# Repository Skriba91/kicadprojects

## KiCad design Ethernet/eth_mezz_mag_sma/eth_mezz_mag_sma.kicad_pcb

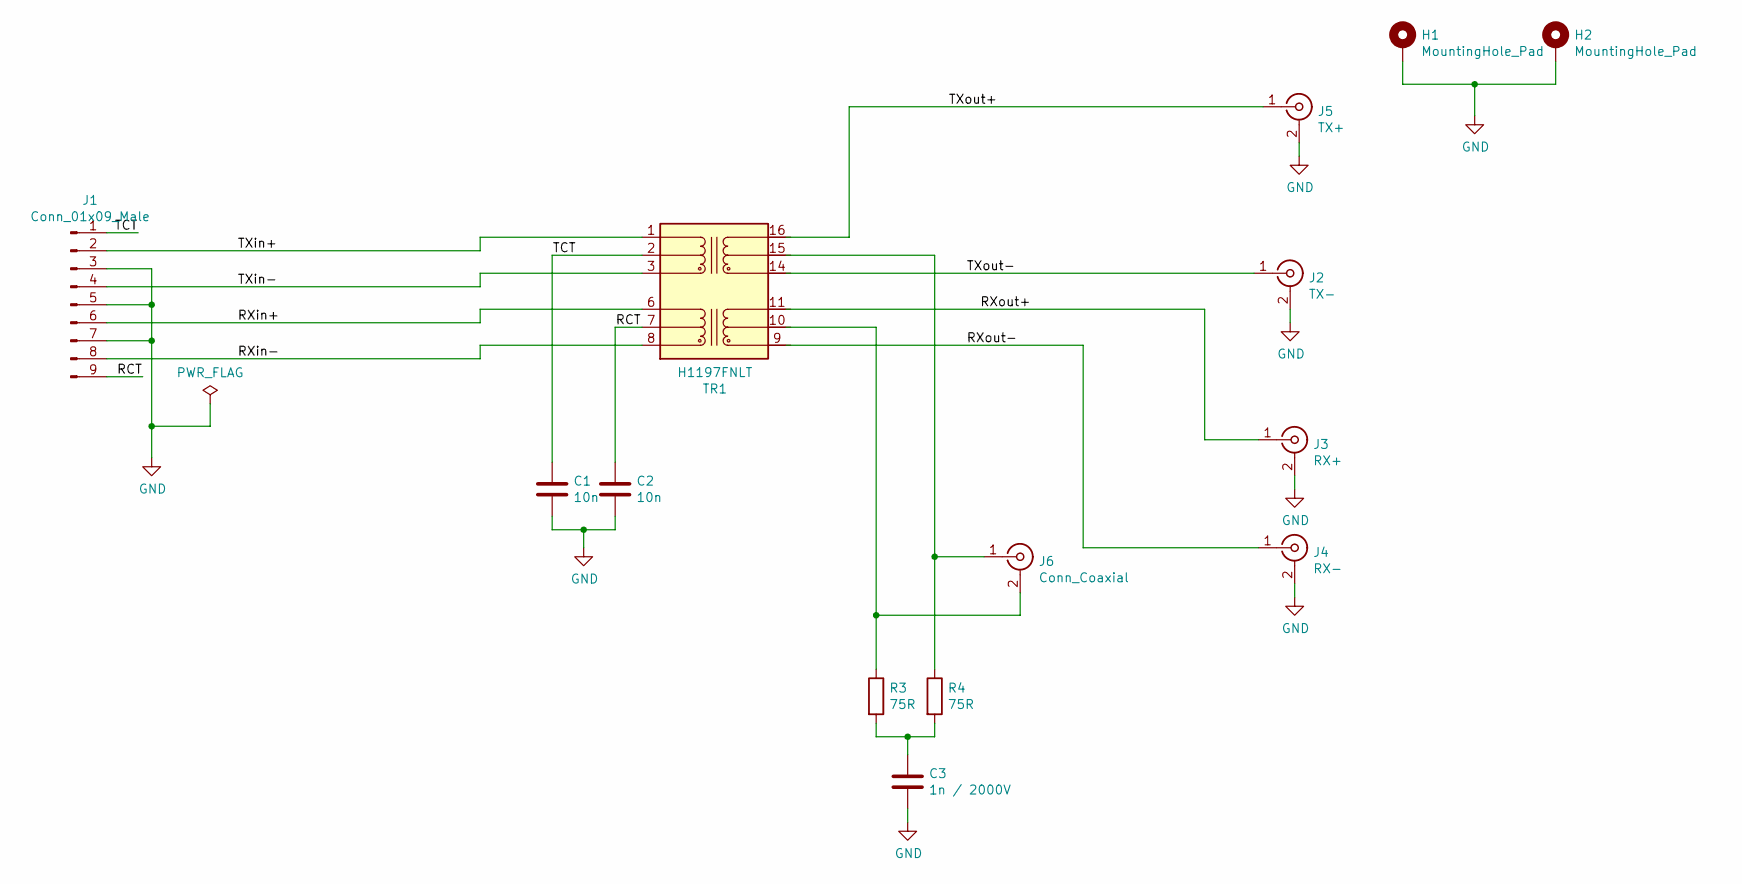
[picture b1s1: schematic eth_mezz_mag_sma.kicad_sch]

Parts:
C1, C2: 10n; C_0805_2012Metric_Pad1.18x1.45mm_HandSolder
C3: 1n / 2000V; R_1206_3216Metric_Pad1.42x1.75mm_HandSolder
H1, H2: MountingHole_Pad; MountingHole_3.2mm_M3_Pad_Via
J1: Conn_01x09_Male; mezzanine_9p_10162582-1134109LF_Conan_1mm
J2: TX-; SMA_Amphenol_132134_Vertical
J3: RX+; SMA_Amphenol_132134_Vertical
J4: RX-; SMA_Amphenol_132134_Vertical
J5: TX+; SMA_Amphenol_132134_Vertical
J6: Conn_Coaxial; BNC_TEConnectivity_1478204_Vertical
R3, R4: 75R; R_0805_2012Metric_Pad1.20x1.40mm_HandSolder
TR1: H1197FNLT; Transformer_Ethernet_Bourns_PT61017PEL

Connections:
/RCT: C2.1, J1.9, TR1.7 (C_RD)
/RXin+: J1.6, TR1.6 (RD+)
/RXin-: J1.8, TR1.8 (RD-)
/RXout+: J3.1 (In), TR1.11 (RX+)
/RXout-: J4.1 (In), TR1.9 (RX-)
/TCT: C1.1, J1.1, TR1.2 (C_TD)
/TXin+: J1.2, TR1.1 (TD+)
/TXin-: J1.4, TR1.3 (TD-)
/TXout+: J5.1 (In), TR1.16 (TX+)
/TXout-: J2.1 (In), TR1.14 (TX-)
GND: C1.2, C2.2, C3.2, H1.1, H2.1, J1.3, J1.5, J1.7, J2.2 (Ext), J3.2 (Ext), J4.2 (Ext), J5.2 (Ext)
unnamed: C3.1, R3.2, R4.2
unnamed: J6.1 (In), R4.1, TR1.15 (C_TX)
unnamed: J6.2 (Ext), R3.1, TR1.10 (C_RX)

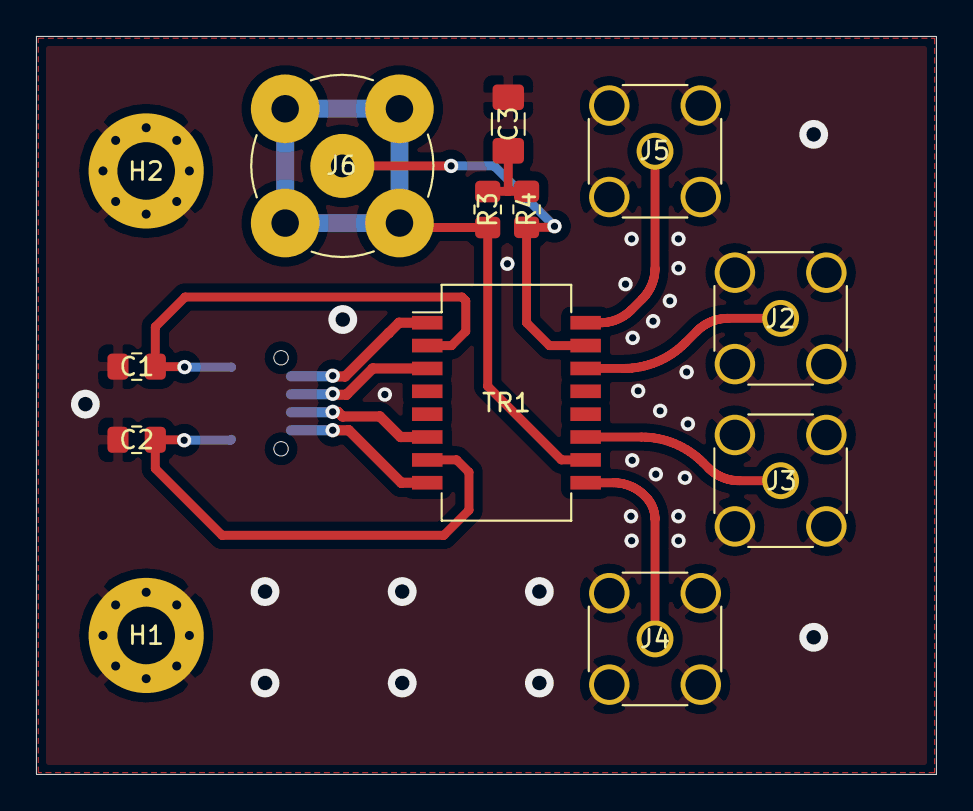
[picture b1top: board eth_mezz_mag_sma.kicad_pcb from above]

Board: 2 copper layers, 50.0 x 41.0 mm, 14 parts (1 on the bottom side), 14 nets.

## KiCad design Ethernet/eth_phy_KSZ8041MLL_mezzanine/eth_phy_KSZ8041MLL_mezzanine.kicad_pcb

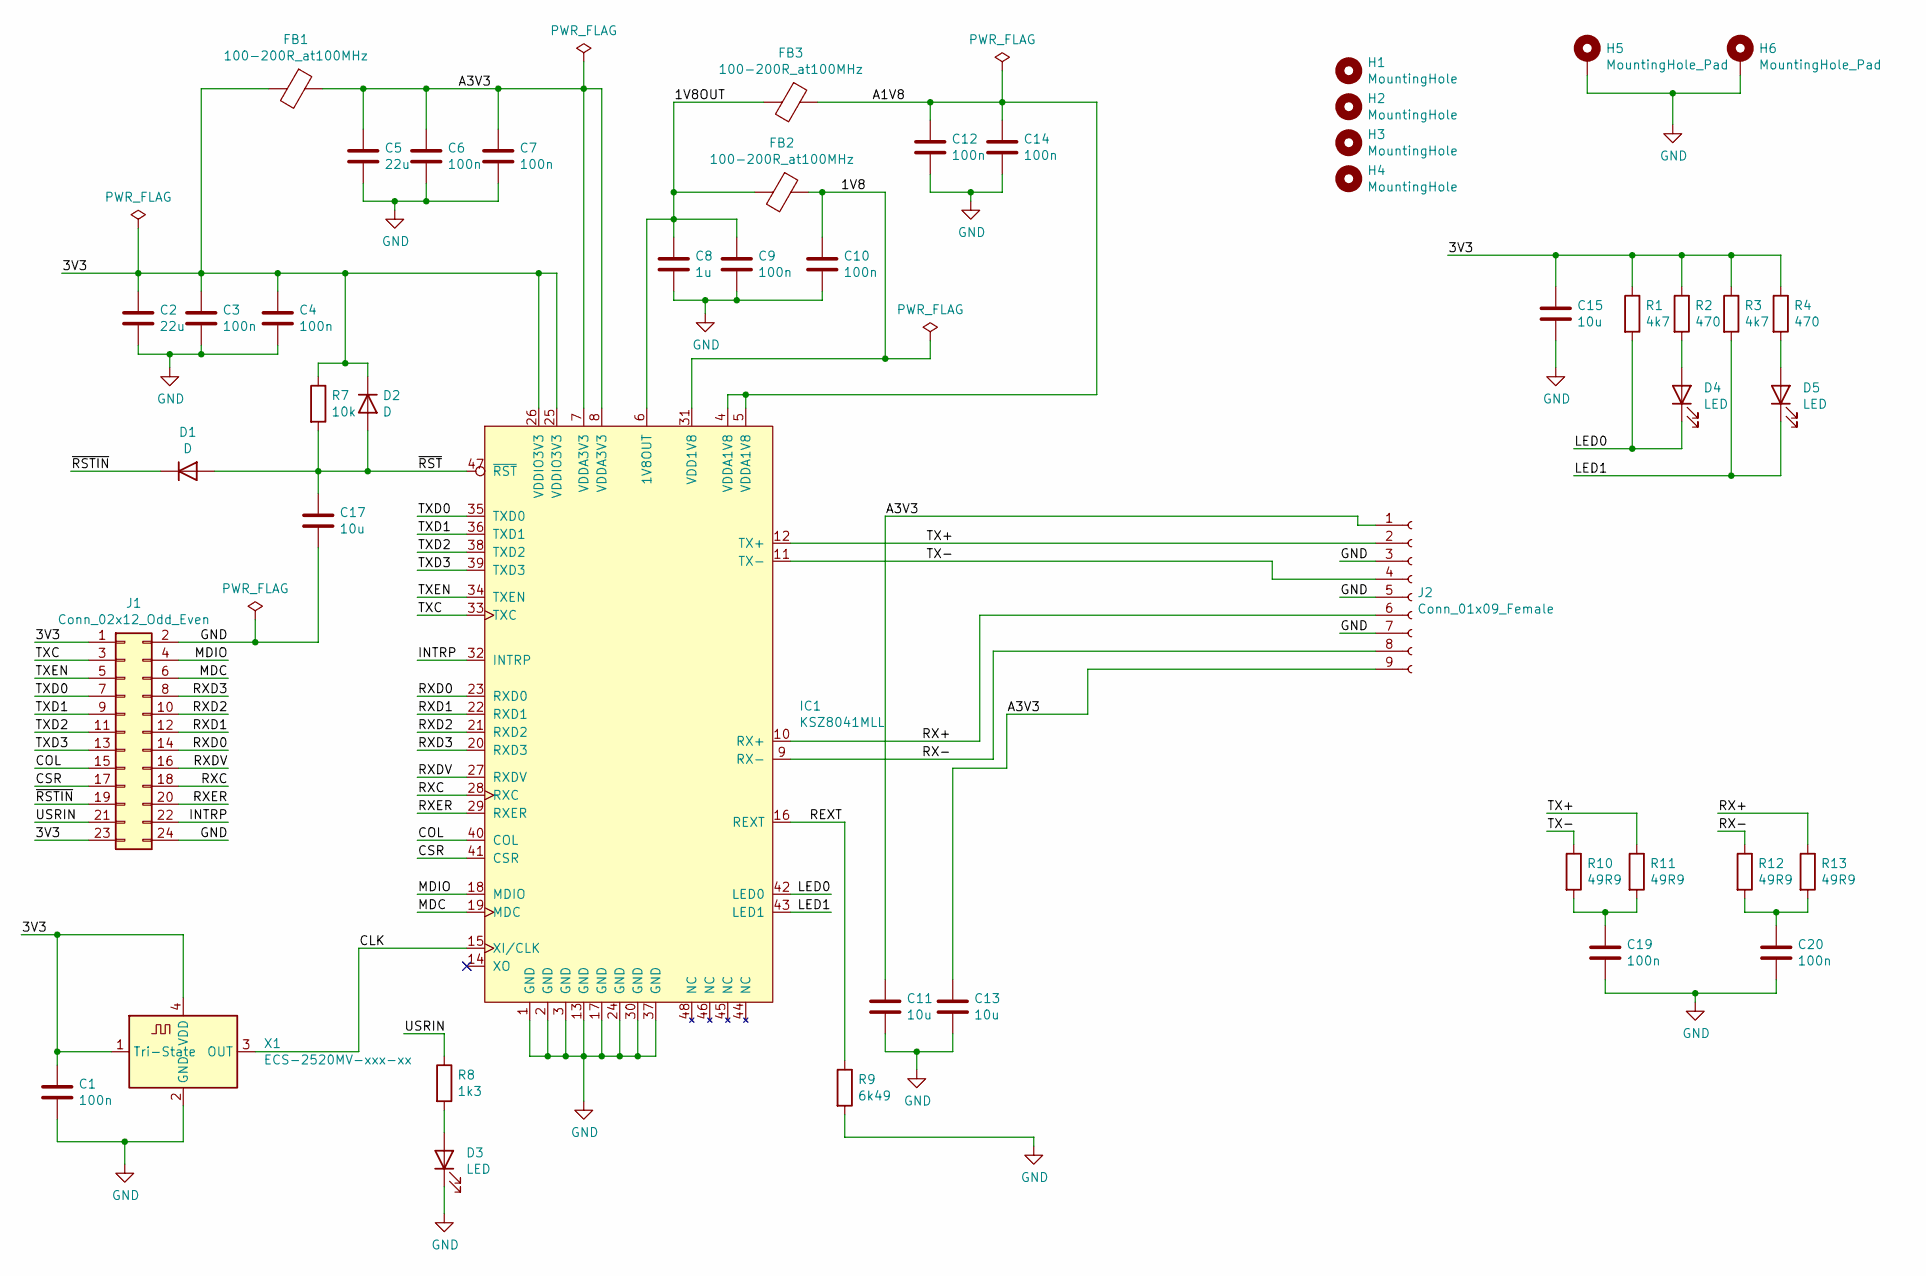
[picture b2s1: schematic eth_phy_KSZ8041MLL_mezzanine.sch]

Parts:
C1, C3, C4, C6, C7, C9, C10, C12, C14, C19, C20: 100n; C_0603_1608Metric_Pad1.08x0.95mm_HandSolder
C2: 22u; C_1206_3216Metric_Pad1.33x1.80mm_HandSolder
C5: 22u; C_1206_3216Metric_Pad1.42x1.75mm_HandSolder
C8: 1u; C_0603_1608Metric_Pad1.08x0.95mm_HandSolder
C11, C13: 10u; C_0603_1608Metric_Pad1.08x0.95mm_HandSolder
C15: 10u; C_0805_2012Metric_Pad1.18x1.45mm_HandSolder
C17: 10u; C_1206_3216Metric_Pad1.42x1.75mm_HandSolder
D1, D2: D; D_MiniMELF_Handsoldering
D3, D4, D5: LED; LED_0805_2012Metric_Pad1.15x1.40mm_HandSolder
FB1, FB2, FB3: 100-200R_at100MHz; L_0805_2012Metric_Pad1.15x1.40mm_HandSolder
H1, H2, H3, H4: MountingHole; MountingHole_3.2mm_M3_Pad_Via
H5, H6: MountingHole_Pad; MountingHole_3.2mm_M3_Pad_Via
IC1: KSZ8041MLL; LQFP-48_7x7mm_P0.5mm
J1: Conn_02x12_Odd_Even; PinHeader_2x12_P2.54mm_Horizontal
J2: Conn_01x09_Female; mezzanine_9p_10162582-1134109LF_Conan_1mm
R1, R3: 4k7; R_0805_2012Metric_Pad1.20x1.40mm_HandSolder
R2, R4: 470; R_0805_2012Metric_Pad1.20x1.40mm_HandSolder
R7: 10k; R_0603_1608Metric_Pad1.05x0.95mm_HandSolder
R8: 1k3; R_0603_1608Metric_Pad1.05x0.95mm_HandSolder
R9: 6k49; R_0603_1608Metric_Pad1.05x0.95mm_HandSolder
R10, R11, R12, R13: 49R9; R_0603_1608Metric_Pad1.05x0.95mm_HandSolder
X1: ECS-2520MV-xxx-xx; Oscillator_SMD_ECS_2520MV-xxx-xx-4Pin_2.5x2.0mm_HANDSOLD

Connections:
/1V8: C10.1, FB2.1, IC1.31 (VDD1V8)
/1V8OUT: C8.1, C9.1, FB2.2, FB3.2, IC1.6 (1V8OUT)
/3V3: C1.1, C2.1, C3.1, C4.1, C15.1, D2.1 (K), FB1.2, IC1.25 (VDDIO3V3), IC1.26 (VDDIO3V3), J1.1, J1.23, R1.1, R2.1, R3.1, R4.1, R7.1, X1.1 (Tri-State), X1.4 (VDD)
/A1V8: C12.1, C14.1, FB3.1, IC1.4 (VDDA1V8), IC1.5 (VDDA1V8)
/A3V3: C5.1, C6.1, C7.1, C11.1, C13.1, FB1.1, IC1.7 (VDDA3V3), IC1.8 (VDDA3V3), J2.1, J2.9
/CLK: IC1.15 (XI/CLK), X1.3 (OUT)
/COL: IC1.40 (COL), J1.15
/CSR: IC1.41 (CSR), J1.17
/INTRP: IC1.32 (INTRP), J1.22
/LED0: D4.1 (K), IC1.42 (LED0), R1.2
/LED1: D5.1 (K), IC1.43 (LED1), R3.2
/MDC: IC1.19 (MDC), J1.6
/MDIO: IC1.18 (MDIO), J1.4
/REXT: IC1.16 (REXT), R9.1
/RX+: IC1.10 (RX+), J2.6, R13.1
/RX-: IC1.9 (RX-), J2.8, R12.1
/RXC: IC1.28 (RXC), J1.18
/RXD0: IC1.23 (RXD0), J1.14
/RXD1: IC1.22 (RXD1), J1.12
/RXD2: IC1.21 (RXD2), J1.10
/RXD3: IC1.20 (RXD3), J1.8
/RXDV: IC1.27 (RXDV), J1.16
/RXER: IC1.29 (RXER), J1.20
/TX+: IC1.12 (TX+), J2.2, R11.1
/TX-: IC1.11 (TX-), J2.4, R10.1
/TXC: IC1.33 (TXC), J1.3
/TXD0: IC1.35 (TXD0), J1.7
/TXD1: IC1.36 (TXD1), J1.9
/TXD2: IC1.38 (TXD2), J1.11
/TXD3: IC1.39 (TXD3), J1.13
/TXEN: IC1.34 (TXEN), J1.5
/USRIN: J1.21, R8.1
/~RST: C17.1, D1.2 (A), D2.2 (A), IC1.47 (~RST), R7.2
/~RSTIN: D1.1 (K), J1.19
GND: C1.2, C2.2, C3.2, C4.2, C5.2, C6.2, C7.2, C8.2, C9.2, C10.2, C11.2, C12.2, C13.2, C14.2, C15.2, C17.2, C19.2, C20.2, D3.1 (K), H5.1, H6.1, IC1.1 (GND), IC1.2 (GND), IC1.3 (GND), IC1.13 (GND), IC1.17 (GND), IC1.24 (GND), IC1.30 (GND), IC1.37 (GND), J1.2, J1.24, J2.3, J2.5, J2.7, R9.2, X1.2 (GND)
unnamed: C19.1, R10.2, R11.2
unnamed: C20.1, R12.2, R13.2
unnamed: D3.2 (A), R8.2
unnamed: D4.2 (A), R2.2
unnamed: D5.2 (A), R4.2

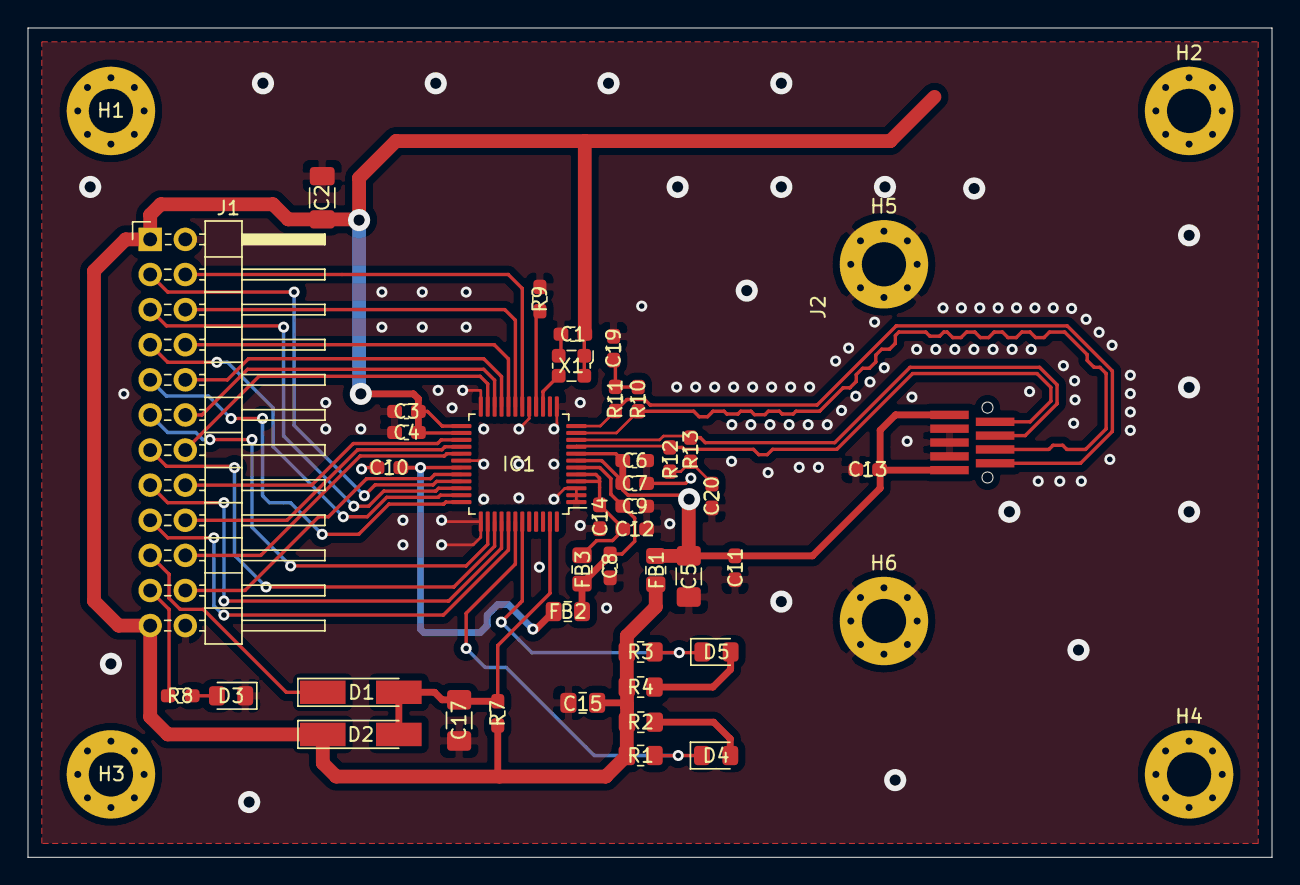
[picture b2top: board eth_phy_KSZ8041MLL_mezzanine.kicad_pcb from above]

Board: 2 copper layers, 90.0 x 60.0 mm, 47 parts (0 on the bottom side), 40 nets.

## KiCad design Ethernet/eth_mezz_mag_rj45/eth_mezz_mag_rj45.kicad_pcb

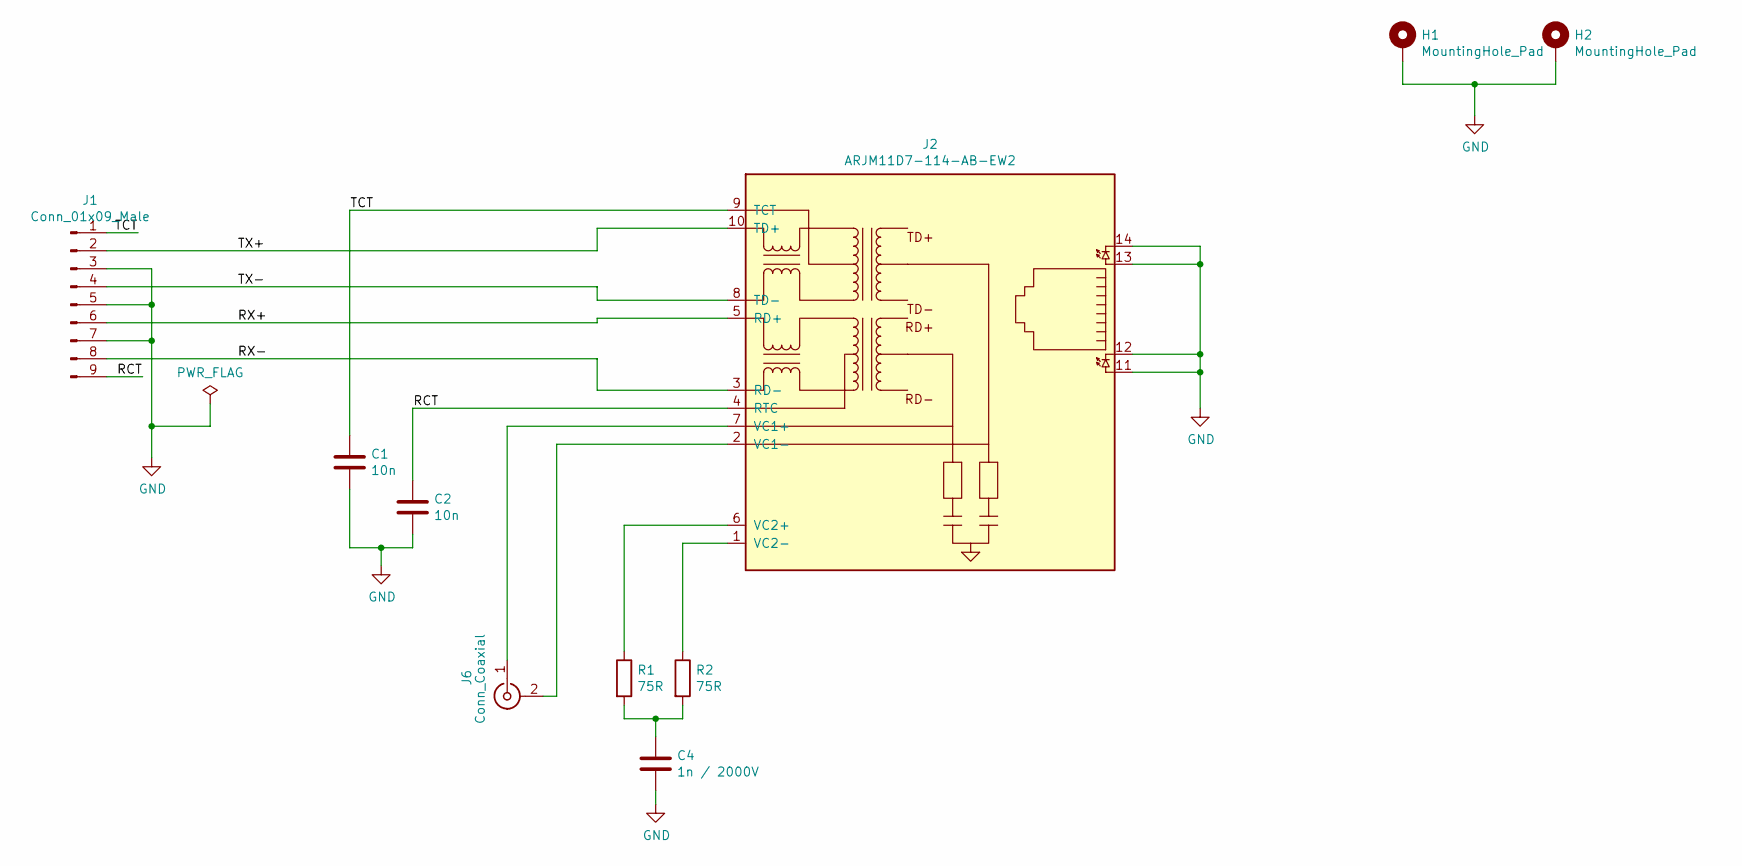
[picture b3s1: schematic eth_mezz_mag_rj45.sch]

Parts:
C1, C2: 10n; C_0805_2012Metric_Pad1.18x1.45mm_HandSolder
C4: 1n / 2000V; R_1206_3216Metric_Pad1.42x1.75mm_HandSolder
H1, H2: MountingHole_Pad; MountingHole_3.2mm_M3_Pad_Via
J1: Conn_01x09_Male; mezzanine_9p_10162582-1134109LF_Conan_1mm
J2: ARJM11D7-114-AB-EW2
J6: Conn_Coaxial; BNC_TEConnectivity_1478204_Vertical
R1, R2: 75R; R_0805_2012Metric_Pad1.20x1.40mm_HandSolder

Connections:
/RCT: C2.1, J1.9, J2.4 (RTC)
/RX+: J1.6, J2.5 (RD+)
/RX-: J1.8, J2.3 (RD-)
/TCT: C1.1, J1.1, J2.9 (TCT)
/TX+: J1.2, J2.10 (TD+)
/TX-: J1.4, J2.8 (TD-)
GND: C1.2, C2.2, C4.2, H1.1, H2.1, J1.3, J1.5, J1.7, J2.11, J2.12, J2.13, J2.14
unnamed: C4.1, R1.2, R2.2
unnamed: J2.1 (VC2-), R2.1
unnamed: J2.2 (VC1-), J6.2 (Ext)
unnamed: J2.6 (VC2+), R1.1
unnamed: J2.7 (VC1+), J6.1 (In)

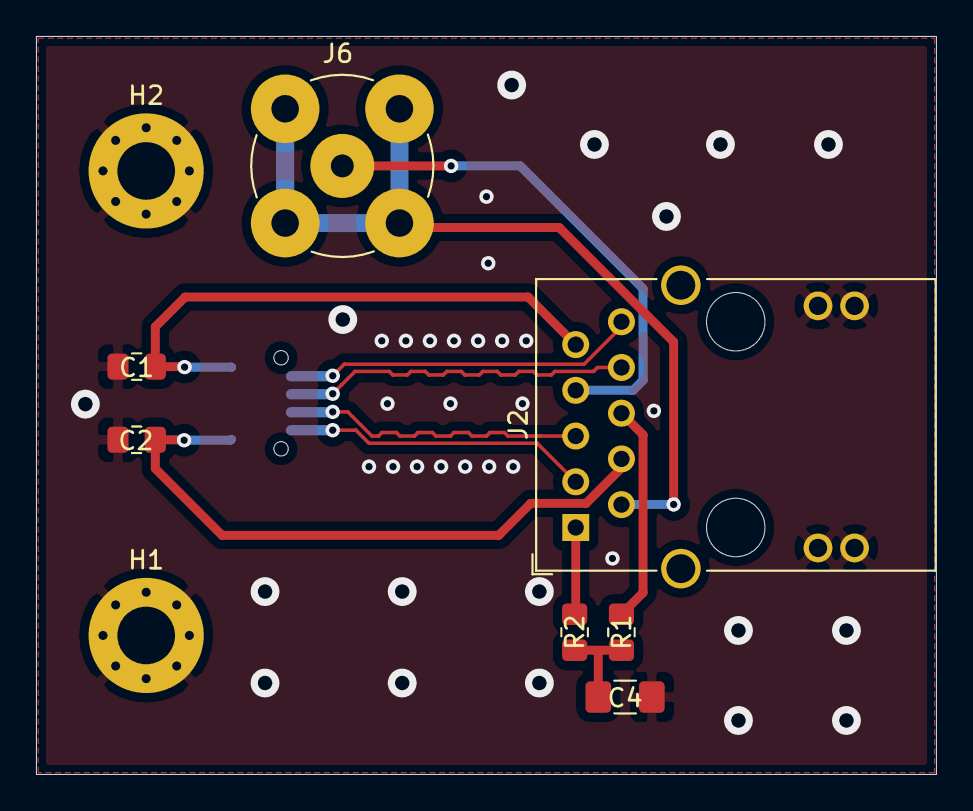
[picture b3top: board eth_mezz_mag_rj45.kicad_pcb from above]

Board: 2 copper layers, 50.0 x 41.0 mm, 10 parts (1 on the bottom side), 12 nets.

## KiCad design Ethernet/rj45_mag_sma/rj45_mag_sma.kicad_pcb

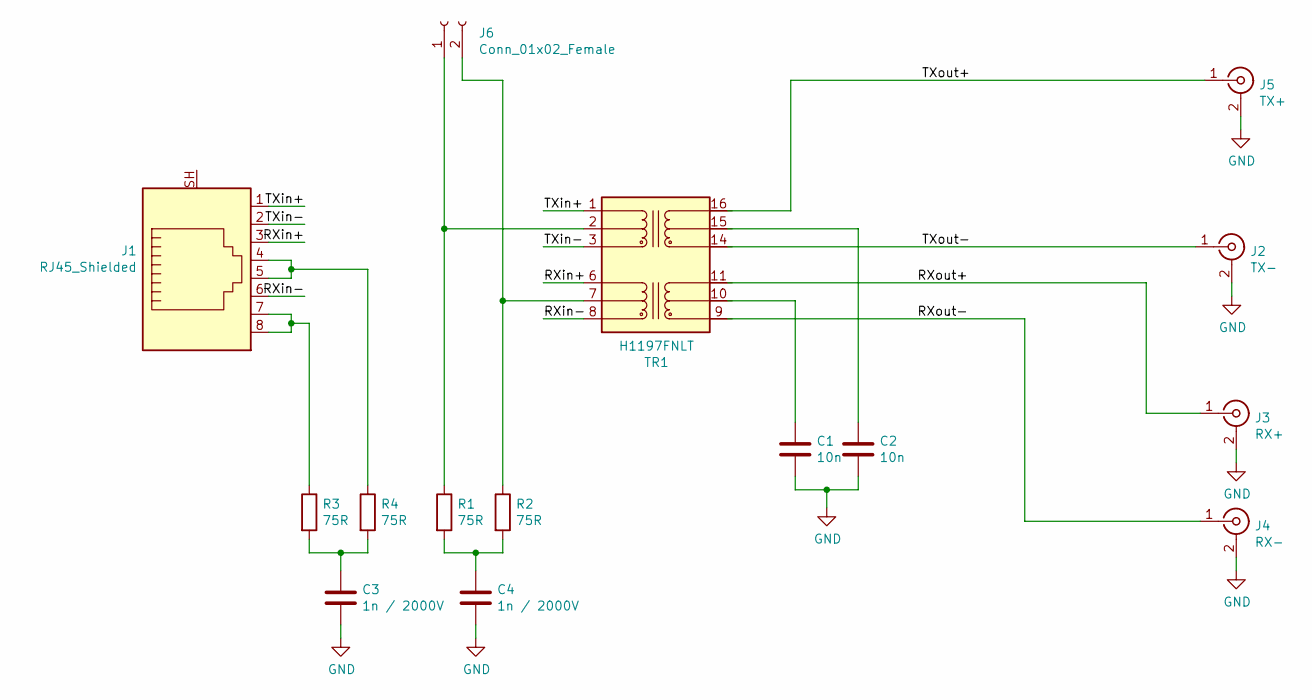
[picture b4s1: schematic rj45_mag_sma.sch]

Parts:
C1, C2: 10n; C_0805_2012Metric_Pad1.18x1.45mm_HandSolder
C3, C4: 1n / 2000V; R_1206_3216Metric_Pad1.42x1.75mm_HandSolder
J1: RJ45_Shielded; RJ45_Ninigi_GE
J2: TX-; SMA_Amphenol_132134_Vertical
J3: RX+; SMA_Amphenol_132134_Vertical
J4: RX-; SMA_Amphenol_132134_Vertical
J5: TX+; SMA_Amphenol_132134_Vertical
J6: Conn_01x02_Female; JWT_A3963_1x02_P3.96mm_Vertical
R1, R2, R3, R4: 75R; R_0805_2012Metric_Pad1.20x1.40mm_HandSolder
TR1: H1197FNLT; Transformer_Ethernet_Bourns_PT61017PEL

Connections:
/RXin+: J1.3, TR1.6 (RD+)
/RXin-: J1.6, TR1.8 (RD-)
/RXout+: J3.1 (In), TR1.11 (RX+)
/RXout-: J4.1 (In), TR1.9 (RX-)
/TXin+: J1.1, TR1.1 (TD+)
/TXin-: J1.2, TR1.3 (TD-)
/TXout+: J5.1 (In), TR1.16 (TX+)
/TXout-: J2.1 (In), TR1.14 (TX-)
GND: C1.2, C2.2, C3.2, C4.2, J1.SH, J2.2 (Ext), J3.2 (Ext), J4.2 (Ext), J5.2 (Ext)
unnamed: C1.1, TR1.10 (C_RX)
unnamed: C2.1, TR1.15 (C_TX)
unnamed: C3.1, R3.2, R4.2
unnamed: C4.1, R1.2, R2.2
unnamed: J1.4, J1.5, R4.1
unnamed: J1.7, J1.8, R3.1
unnamed: J6.1, R1.1, TR1.2 (C_TD)
unnamed: J6.2, R2.1, TR1.7 (C_RD)

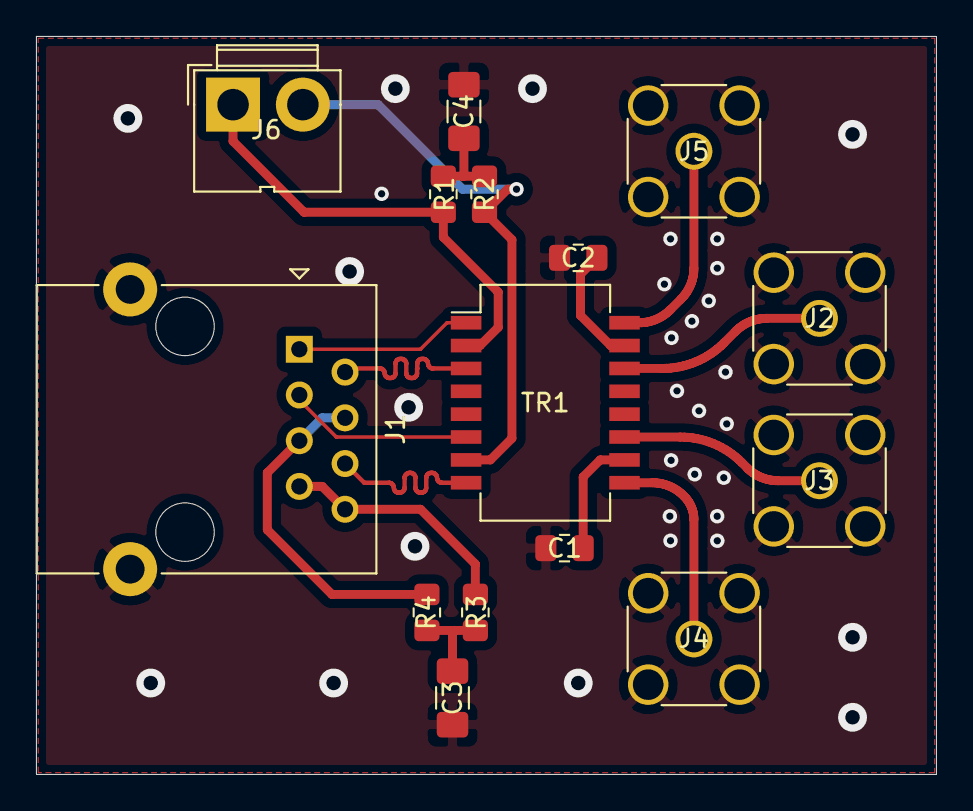
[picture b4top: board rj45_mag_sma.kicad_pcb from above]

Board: 2 copper layers, 50.0 x 41.0 mm, 15 parts (0 on the bottom side), 17 nets.

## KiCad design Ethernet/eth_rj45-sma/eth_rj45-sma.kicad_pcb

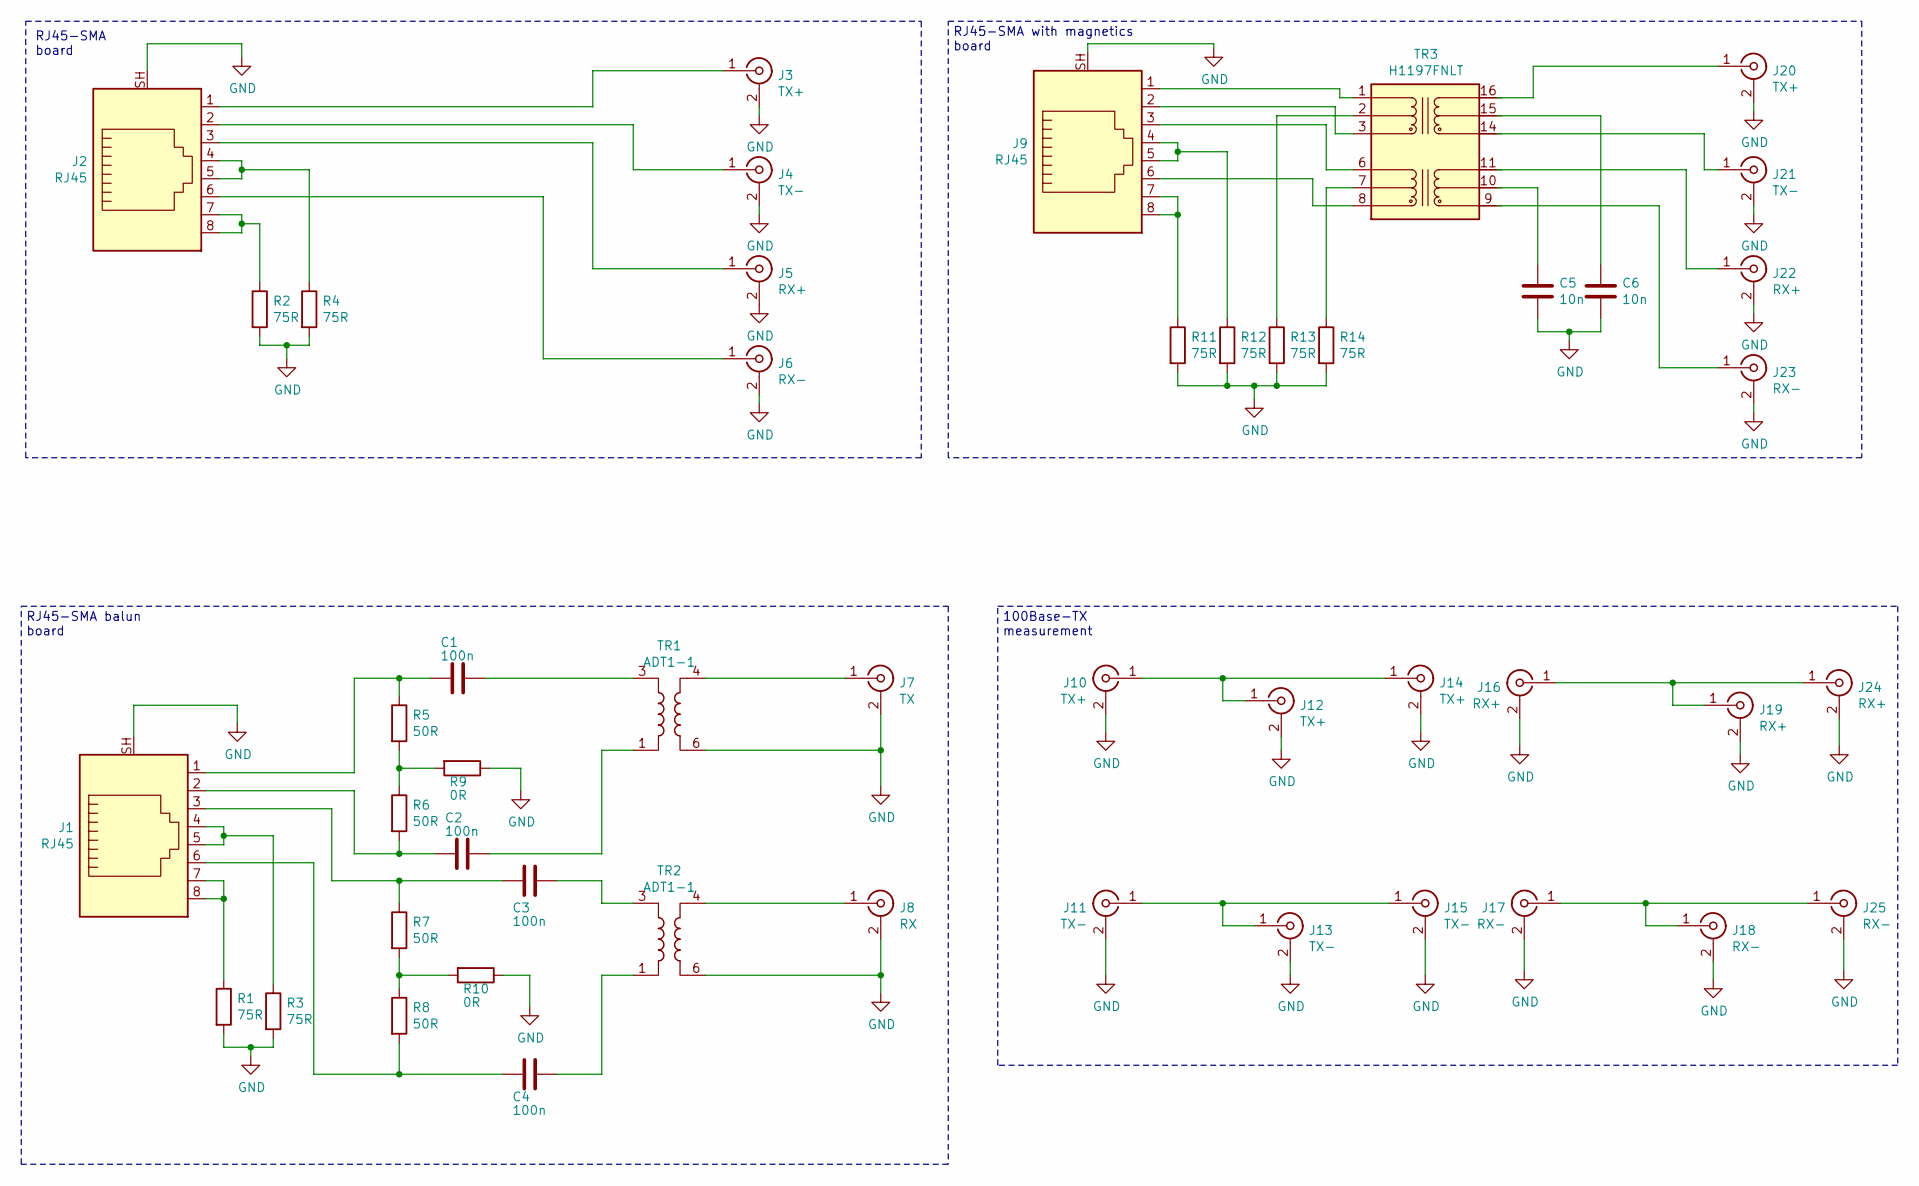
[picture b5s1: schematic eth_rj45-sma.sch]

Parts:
C1, C2, C3, C4: 100n; C_0603_1608Metric_Pad1.05x0.95mm_HandSolder
C5, C6: 10n; C_0603_1608Metric_Pad1.05x0.95mm_HandSolder
J1, J2, J9: RJ45; RJ45_Ninigi_GE
J3, J12, J20: TX+; SMA_Amphenol_132134_Vertical
J4, J13, J21: TX-; SMA_Amphenol_132134_Vertical
J5, J19, J22: RX+; SMA_Amphenol_132134_Vertical
J6, J18, J23: RX-; SMA_Amphenol_132134_Vertical
J7: TX; SMA_Amphenol_132134_Vertical
J8: RX; SMA_Amphenol_132134_Vertical
J10, J14: TX+; SMA_Amphenol_132289_EdgeMount
J11, J15: TX-; SMA_Amphenol_132289_EdgeMount
J16, J24: RX+; SMA_Amphenol_132289_EdgeMount
J17, J25: RX-; SMA_Amphenol_132289_EdgeMount
R1, R2, R3, R4, R11, R12, R13, R14: 75R; R_1206_3216Metric_Pad1.42x1.75mm_HandSolder
R5, R6, R7, R8: 50R; R_0603_1608Metric_Pad1.05x0.95mm_HandSolder
R9, R10: 0R; R_0603_1608Metric_Pad1.05x0.95mm_HandSolder
TR1, TR2: ADT1-1; Mini-Circuits_CD542_H2.84mm
TR3: H1197FNLT; Transformer_Ethernet_Bourns_PT61017PEL

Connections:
GND: C5.2, C6.2, J1.SH, J2.SH, J3.2 (Ext), J4.2 (Ext), J5.2 (Ext), J6.2 (Ext), J7.2 (Ext), J8.2 (Ext), J9.SH, J10.2 (Ext), J11.2 (Ext), J12.2 (Ext), J13.2 (Ext), J14.2 (Ext), J15.2 (Ext), J16.2 (Ext), J17.2 (Ext), J18.2 (Ext), J19.2 (Ext), J20.2 (Ext), J21.2 (Ext), J22.2 (Ext), J23.2 (Ext), J24.2 (Ext), J25.2 (Ext), R1.2, R2.2, R3.2, R4.2, R9.1, R10.1, R11.2, R12.2, R13.2, R14.2, TR1.6, TR2.6
unnamed: C1.1, TR1.3
unnamed: C1.2, J1.1, R5.1
unnamed: C2.1, TR1.1
unnamed: C2.2, J1.2, R6.2
unnamed: C3.1, TR2.3
unnamed: C3.2, J1.3, R7.1
unnamed: C4.1, TR2.1
unnamed: C4.2, J1.6, R8.2
unnamed: C5.1, TR3.10 (C_RX)
unnamed: C6.1, TR3.15 (C_TX)
unnamed: J1.4, J1.5, R3.1
unnamed: J1.7, J1.8, R1.1
unnamed: J2.1, J3.1 (In)
unnamed: J2.2, J4.1 (In)
unnamed: J2.3, J5.1 (In)
unnamed: J2.4, J2.5, R4.1
unnamed: J2.6, J6.1 (In)
unnamed: J2.7, J2.8, R2.1
unnamed: J7.1 (In), TR1.4
unnamed: J8.1 (In), TR2.4
unnamed: J9.1, TR3.1 (TD+)
unnamed: J9.2, TR3.3 (TD-)
unnamed: J9.3, TR3.6 (RD+)
unnamed: J9.4, J9.5, R12.1
unnamed: J9.6, TR3.8 (RD-)
unnamed: J9.7, J9.8, R11.1
unnamed: J10.1 (In), J12.1 (In), J14.1 (In)
unnamed: J11.1 (In), J13.1 (In), J15.1 (In)
unnamed: J16.1 (In), J19.1 (In), J24.1 (In)
unnamed: J17.1 (In), J18.1 (In), J25.1 (In)
unnamed: J20.1 (In), TR3.16 (TX+)
unnamed: J21.1 (In), TR3.14 (TX-)
unnamed: J22.1 (In), TR3.11 (RX+)
unnamed: J23.1 (In), TR3.9 (RX-)
unnamed: R5.2, R6.1, R9.2
unnamed: R7.2, R8.1, R10.2
unnamed: R13.1, TR3.2 (C_TD)
unnamed: R14.1, TR3.7 (C_RD)

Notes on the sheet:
RJ45-SMA board
RJ45-SMA with magnetics board
RJ45-SMA balun board
100Base-TX measurement

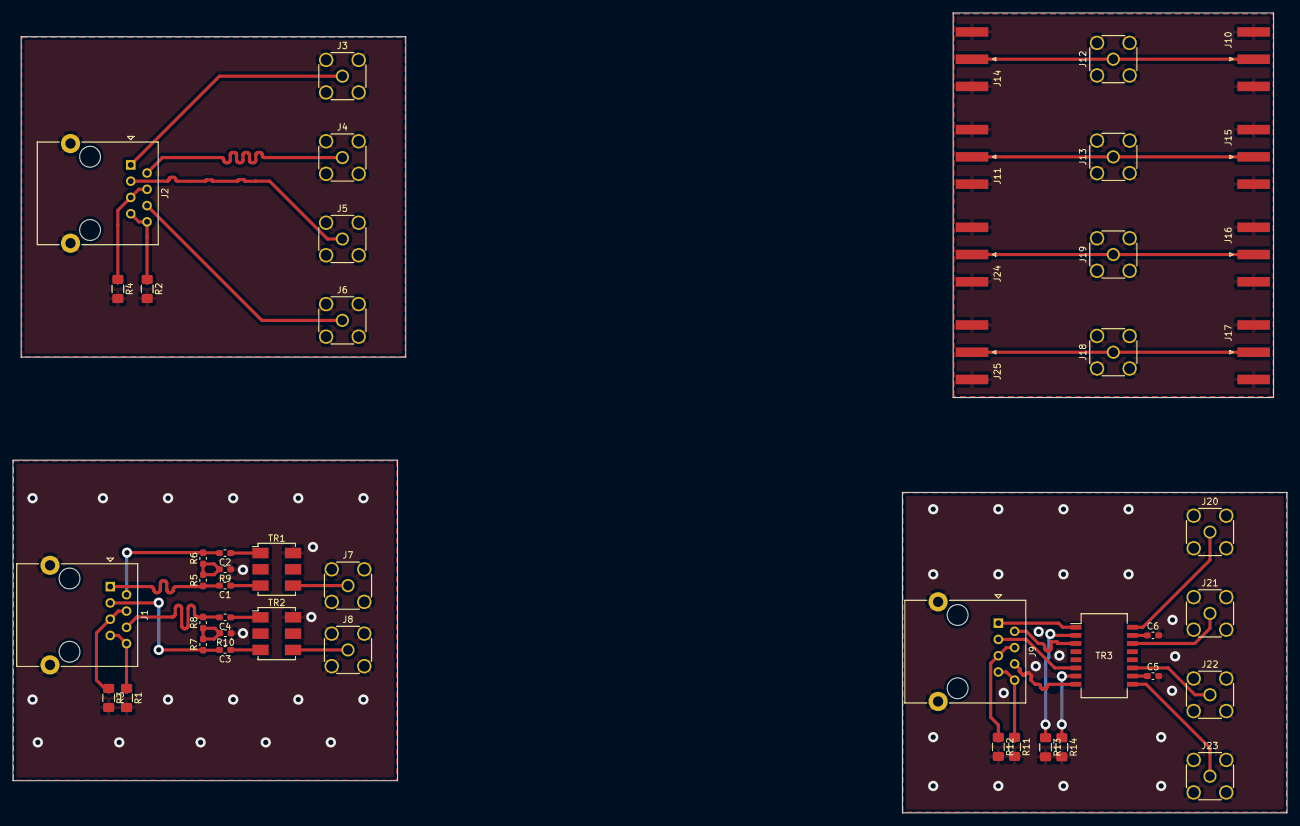
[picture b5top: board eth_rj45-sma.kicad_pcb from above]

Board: 2 copper layers, 198.8 x 124.8 mm, 48 parts (0 on the bottom side), 39 nets.

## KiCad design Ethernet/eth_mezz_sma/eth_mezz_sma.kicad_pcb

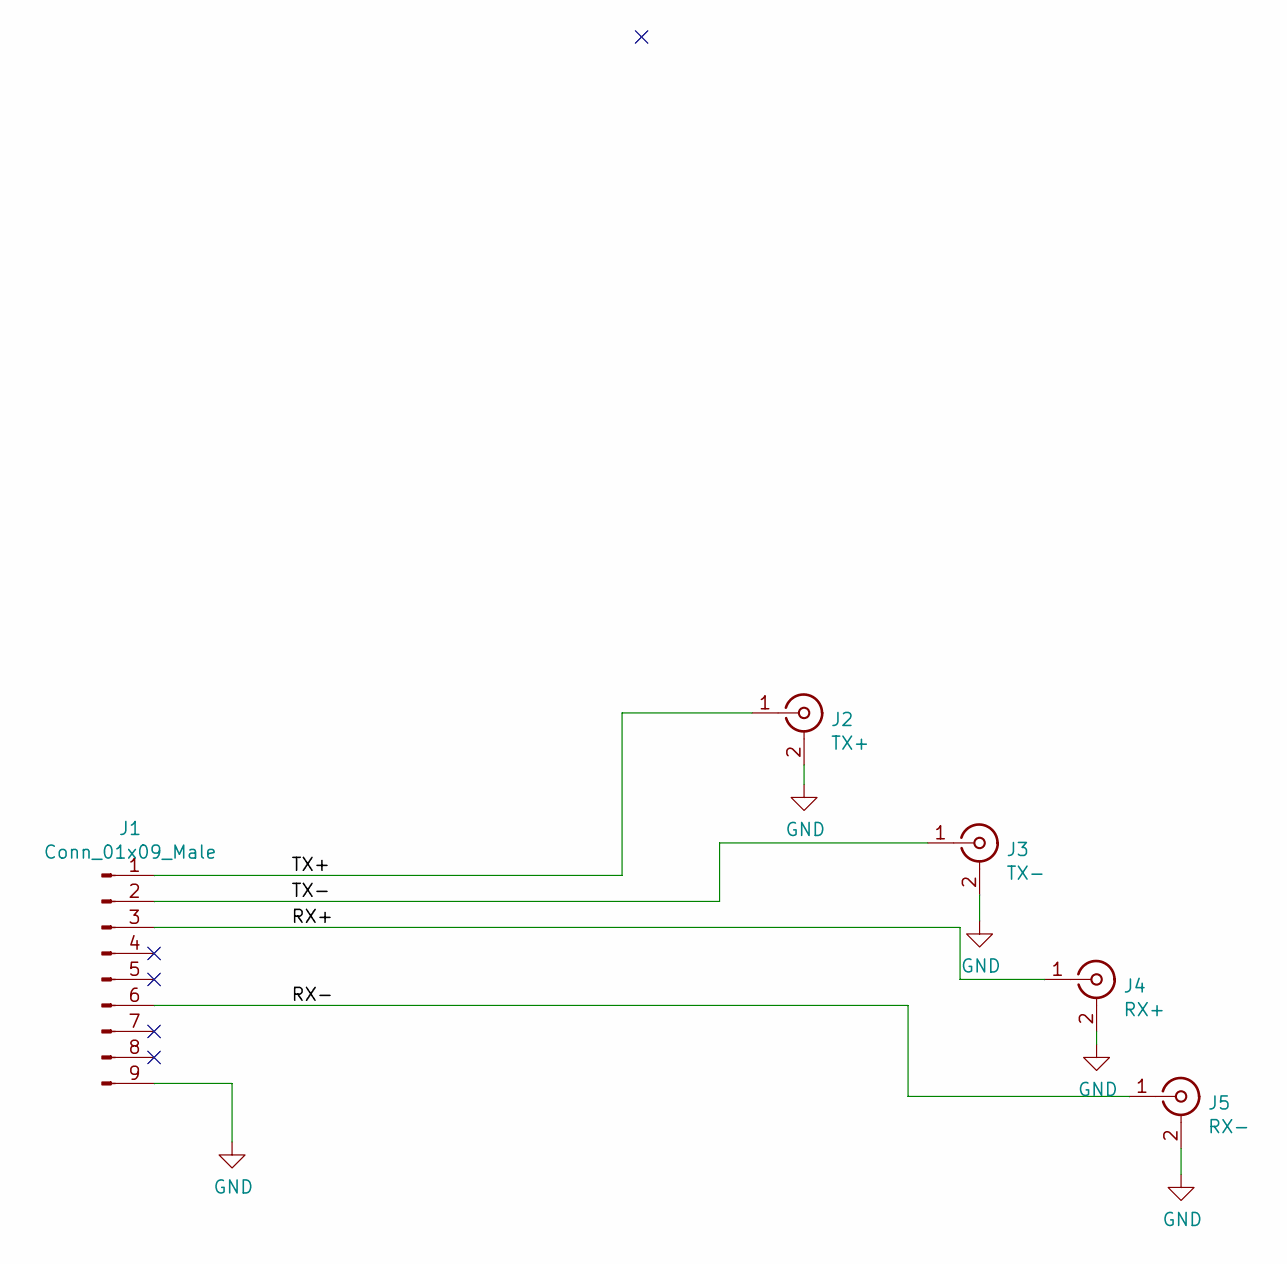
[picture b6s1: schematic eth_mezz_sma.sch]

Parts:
J1: Conn_01x09_Male; mezzanine_9p_10162582-1134109LF_Conan_1mm
J2: TX+; SMA_Amphenol_132134_Vertical
J3: TX-; SMA_Amphenol_132134_Vertical
J4: RX+; SMA_Amphenol_132134_Vertical
J5: RX-; SMA_Amphenol_132134_Vertical

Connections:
/RX+: J1.3, J4.1 (In)
/RX-: J1.6, J5.1 (In)
/TX+: J1.1, J2.1 (In)
/TX-: J1.2, J3.1 (In)
GND: J1.9, J2.2 (Ext), J3.2 (Ext), J4.2 (Ext), J5.2 (Ext)

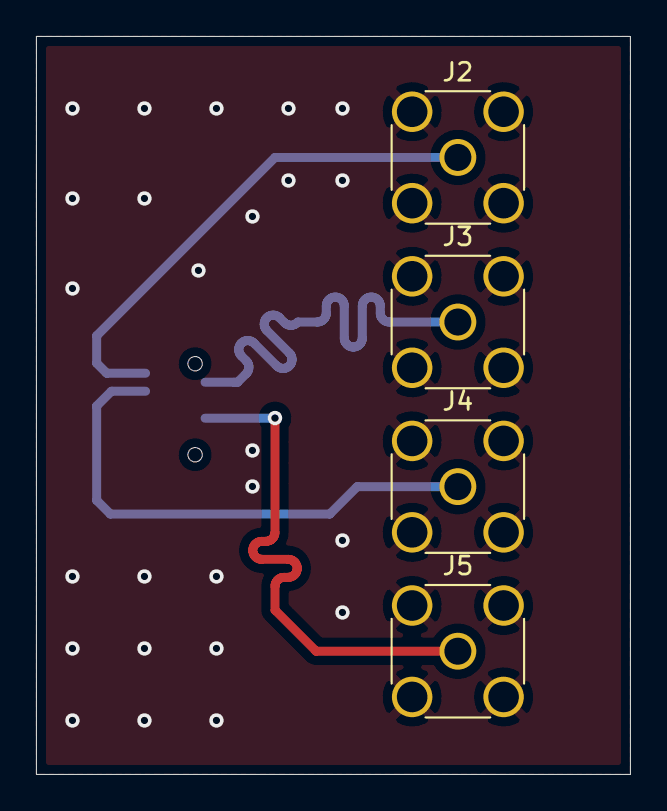
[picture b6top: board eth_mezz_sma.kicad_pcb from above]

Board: 2 copper layers, 33.0 x 41.0 mm, 5 parts (1 on the bottom side), 5 nets.

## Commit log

2021-12-03 SummingCircuitStarted
2021-12-13 SchematicStarted
2021-12-14 EthSMA100Base-TXModuleMezzanine
2021-12-14 Eth-RJ45_adapters_complete
2021-12-14 ProgressWithAnOtherCircuit
2021-12-15 PHY module with RJ45
2021-12-16 SomeBoardsReady
2021-12-17 FirstRoundPanelsDone
2021-12-30 ReferenceNumberPlaced
2022-05-12 Symbolumlibrary with Arty header
2022-05-12 Rokavevo project created
2022-05-12 BPSK transciever, receiver done
2022-05-12 Mixer symbol added
2022-05-12 Arty header footprint
2022-05-12 Gitignore updated to ignore *.zip files
2022-05-13 Comment added
2022-05-13 Arty Signal generatior shield DAC7821IPW priject created
2022-05-13 Arty shield header PCB finished, QMTECH header schematic started
2022-05-13 In production
